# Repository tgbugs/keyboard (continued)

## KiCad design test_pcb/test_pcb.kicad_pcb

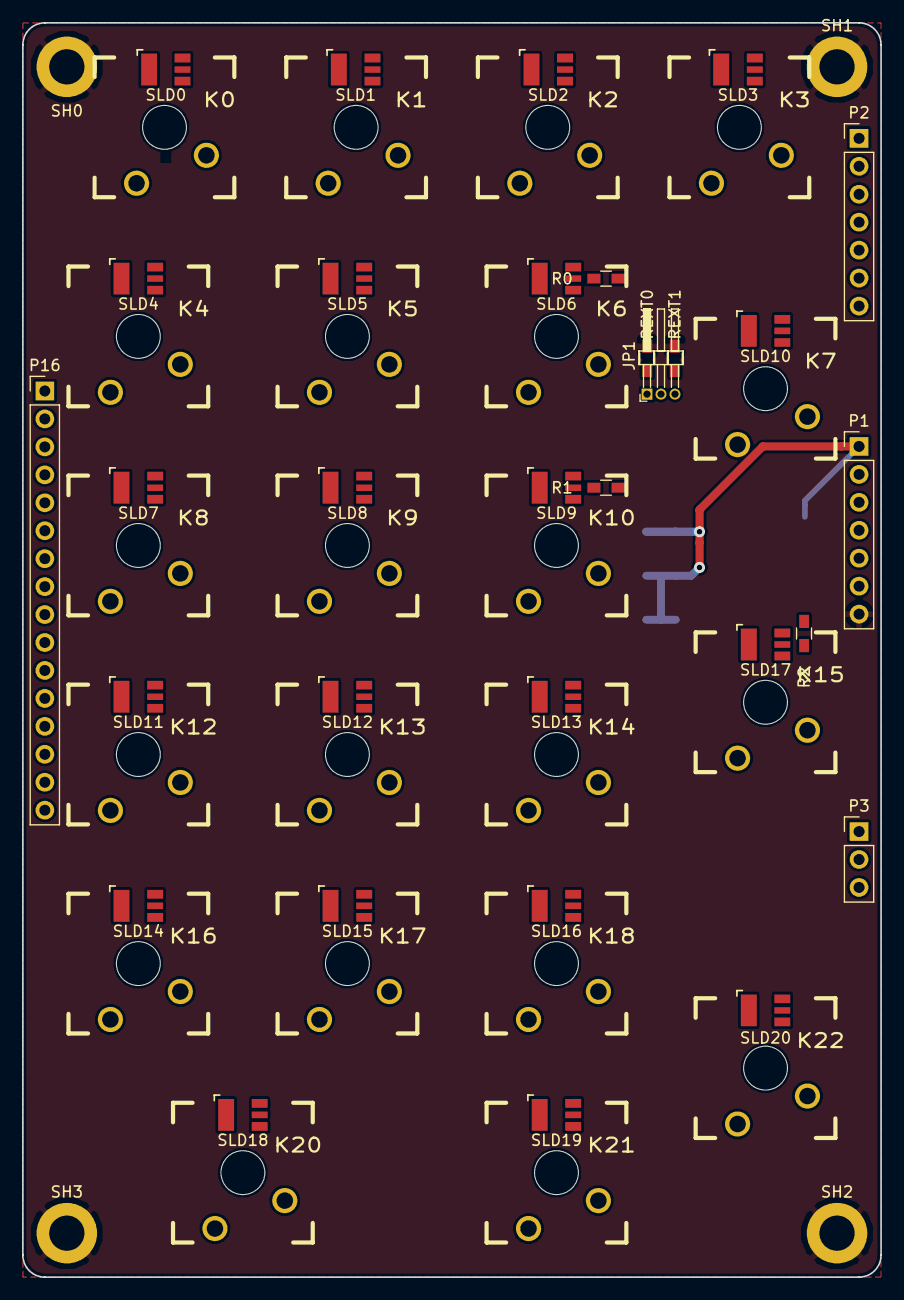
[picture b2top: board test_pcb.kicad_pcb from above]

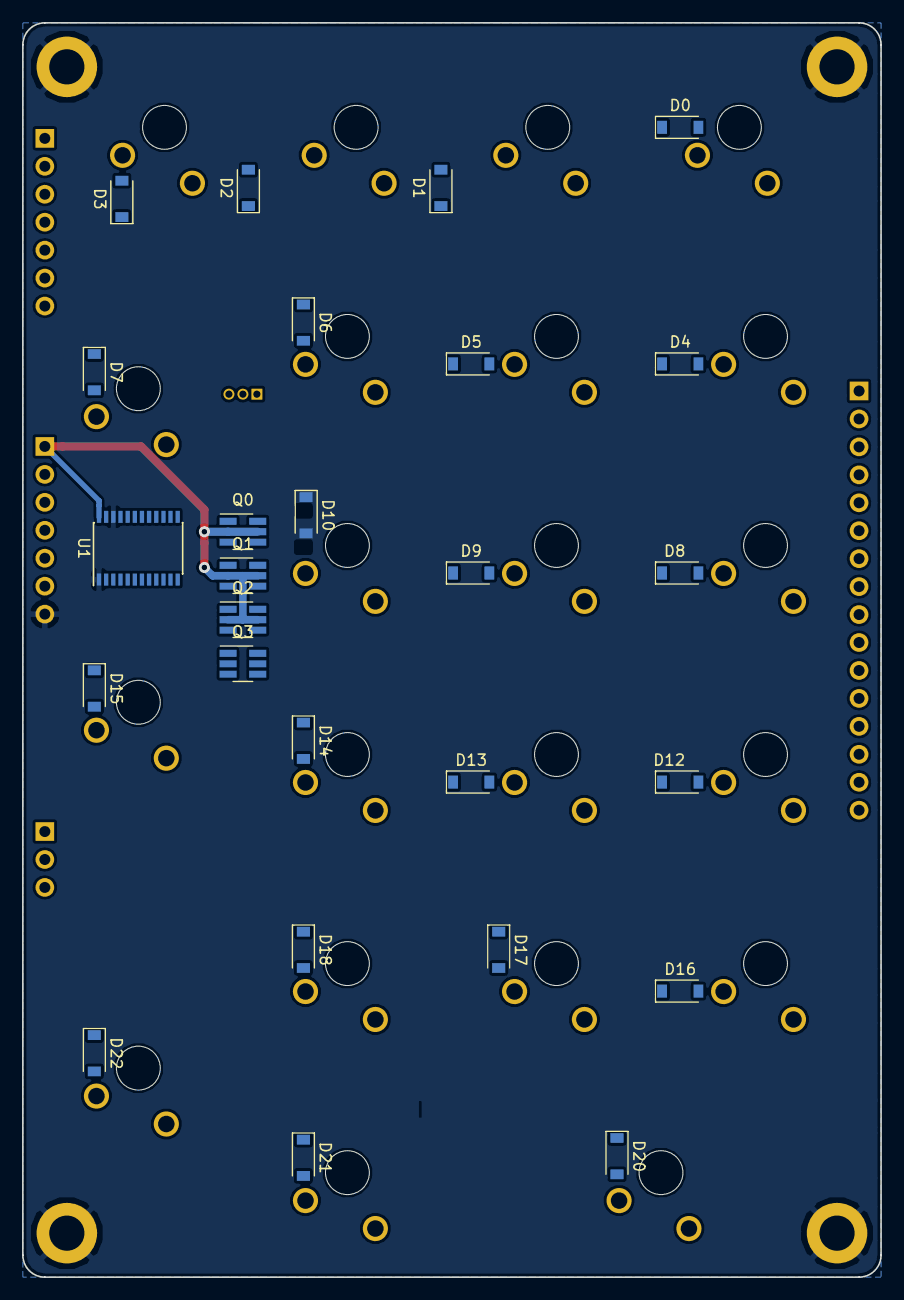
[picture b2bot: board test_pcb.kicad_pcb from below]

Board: 2 copper layers, 78.0 x 114.0 mm, 82 parts (26 on the bottom side), 66 nets.

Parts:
D0, D1, D2, D3, D4, D5, D6, D7, D8, D9, D10, D12, D13, D14, D15, D16, D17, D18, D20, D21, D22: D; D_SOD-123
JP1: Jumper_NC_Dual; Pin_Header_Angled_1x03_Pitch1.27mm
K0, K1, K2, K3: KEYSW; CHERRY_PLATE_91.6H
K4, K5, K6, K8, K9, K10, K12, K13, K14, K16, K17, K18, K21: KEYSW; CHERRY_PLATE_100H
K7, K15: KEYSW; CHERRY_PLATE_150V
K20: KEYSW; CHERRY_PLATE_200H
K22: KEYSW; CHERRY_PLATE_200V
P1, P2: CONN_01X07; Socket_Strip_Straight_1x07_Pitch2.54mm
P3: CONN_01X03; Socket_Strip_Straight_1x03_Pitch2.54mm
P16: CONN_01X16; Socket_Strip_Straight_1x16_Pitch2.54mm
Q0, Q1, Q2, Q3: Si3993CDV; SOT-23-6_Handsoldering
R0, R1, R2: R; R_0603_HandSoldering_label_right
REXT0, REXT1: R; R_0603_HandSoldering_label_right
SH0, SH1, SH2, SH3: CONN_01X01; MountingHole_3.2mm_M3_ISO14580_Pad
SLD0, SLD1, SLD2, SLD3, SLD4, SLD5, SLD6, SLD7, SLD8, SLD9, SLD11, SLD12, SLD13, SLD14, SLD15, SLD16, SLD18, SLD19, SLD20: SMLVN6RGB_CA
SLD10, SLD17: SMLVN6RGB; SMLVN6RGB_CA
U1: STP16CP05; TSSOP-24_4.4x7.8mm_Pitch0.65mm

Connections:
+3V3: P1.1, Q0.2, Q0.5, Q1.2, Q1.5, Q2.2, Q2.5, Q3.5, U1.24
CLK: P1.5, U1.3
GND: P1.7, REXT0.1, REXT1.1, SH0.1, SH1.1, SH2.1, SH3.1, U1.1, U1.22
LE: P1.4, U1.4
unnamed: D0.2, K0.2
unnamed: D1.2, K1.2
unnamed: D2.2, K2.2
unnamed: D3.2, K3.2
unnamed: D4.2, K4.2
unnamed: D5.2, K5.2
unnamed: D6.2, K6.2
unnamed: D7.2, K7.2
unnamed: D8.2, K8.2
unnamed: D9.2, K9.2
unnamed: D10.2, K10.2
unnamed: D12.2, K12.2
unnamed: D13.2, K13.2
unnamed: D14.2, K14.2
unnamed: D15.2, K15.2
unnamed: D16.2, K16.2
unnamed: D17.2, K17.2
unnamed: D18.2, K18.2
unnamed: D20.2, K20.2
unnamed: D21.2, K21.2
unnamed: D22.2, K22.2
unnamed: JP1.1, REXT0.2
unnamed: JP1.3, REXT1.2
unnamed: R0.2, U1.15
unnamed: R1.2, U1.16
unnamed: R2.2, U1.17
OE: P1.3, U1.21
SDI: P1.6, U1.2
a0: Q0.6, SLD0.1, SLD7.1, SLD14.1
a1: Q0.4, SLD1.1, SLD8.1, SLD15.1
a2: Q1.6, SLD2.1, SLD9.1, SLD16.1
a3: Q1.4, SLD3.1, SLD10.1, SLD17.1
a4: Q2.6, SLD4.1, SLD11.1, SLD18.1
a5: Q2.4, SLD5.1, SLD12.1, SLD19.1
a6: Q3.6, SLD6.1, SLD13.1, SLD20.1
as0: P16.7, Q0.1, U1.6
as1: P16.8, Q0.3, U1.7
as2: P16.9, Q1.1, U1.8
as3: P16.10, Q1.3, U1.9
as4: P16.11, Q2.1, U1.10
as5: P16.12, Q2.3, U1.11
as6: P16.13, Q3.1, U1.12
blue0: P16.1, SLD0.6, SLD1.6, SLD2.6, SLD3.6, SLD4.6, SLD5.6, SLD6.6, U1.20
blue1: P16.4, SLD7.6, SLD8.6, SLD9.6, SLD10.6, SLD11.6, SLD12.6, SLD13.6, U1.19
blue2: P16.14, SLD14.6, SLD15.6, SLD16.6, SLD17.6, SLD18.6, SLD19.6, SLD20.6, U1.18
c0: D0.1, D4.1, D8.1, D12.1, D16.1, D20.1, P2.1
c1: D1.1, D5.1, D9.1, D13.1, D17.1, P2.3
c2: D2.1, D6.1, D10.1, D14.1, D18.1, D21.1, P2.4
c3: D3.1, D7.1, D15.1, D22.1, P2.5
green0: P16.3, SLD0.4, SLD1.4, SLD2.4, SLD3.4, SLD4.4, SLD5.4, SLD6.4, U1.14
green1: P16.6, SLD7.4, SLD8.4, SLD9.4, SLD10.4, SLD11.4, SLD12.4, SLD13.4, U1.13
green2: P16.16, SLD14.4, SLD15.4, SLD16.4, SLD17.4, SLD18.4, SLD19.4, SLD20.4, U1.5
r0: K0.1, K1.1, K2.1, K3.1, P2.2
r1: K4.1, K5.1, K6.1, K7.1, P2.6
r2: K8.1, K9.1, K10.1, P2.7
r3: K12.1, K13.1, K14.1, K15.1, P3.1
r4: K16.1, K17.1, K18.1, P3.2
r5: K20.1, K21.1, K22.1, P3.3
red0: P16.2, R0.1, SLD0.5, SLD1.5, SLD2.5, SLD3.5, SLD4.5, SLD5.5, SLD6.5
red1: P16.5, R1.1, SLD7.5, SLD8.5, SLD9.5, SLD10.5, SLD11.5, SLD12.5, SLD13.5
red2: P16.15, R2.1, SLD14.5, SLD15.5, SLD16.5, SLD17.5, SLD18.5, SLD19.5, SLD20.5
rext: JP1.2, P1.2, U1.23

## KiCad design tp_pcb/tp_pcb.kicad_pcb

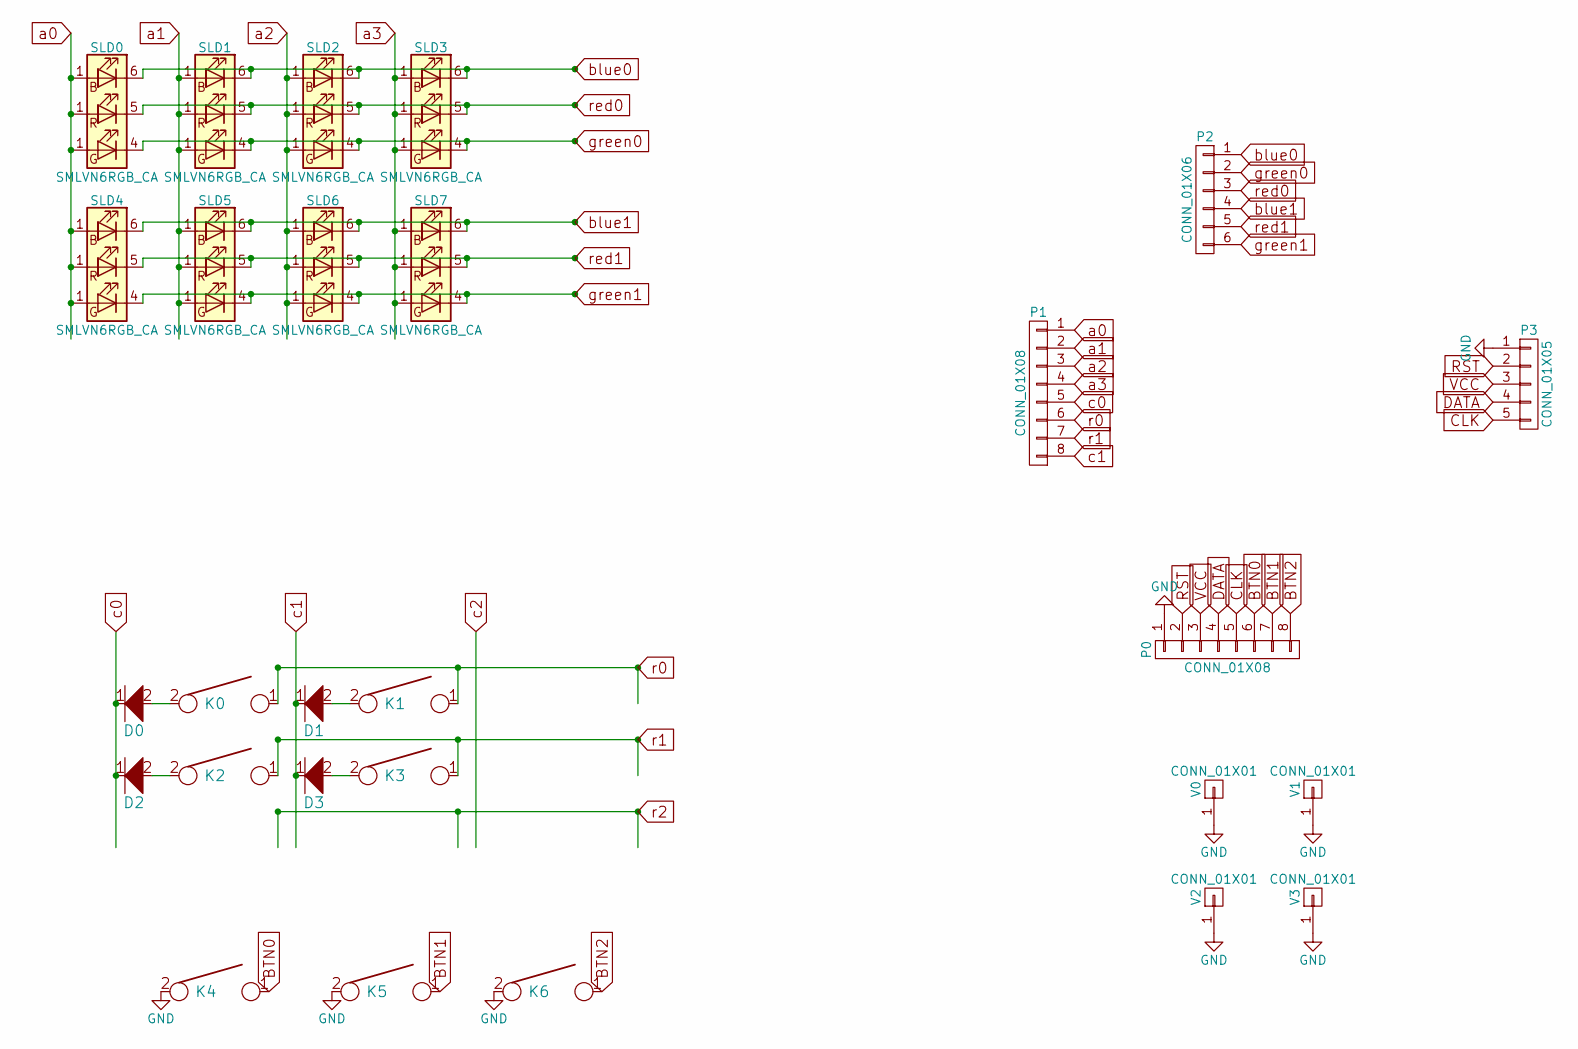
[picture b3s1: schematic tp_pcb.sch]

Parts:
D0, D1, D2, D3: D; D_SOD-123
K0, K1, K2, K5: KEYSW; CHERRY_PLATE_NH_100H
K3: KEYSW; CHERRY_PLATE_NH_5000H
K4, K6: KEYSW; CHERRY_PLATE_175H
P0: CONN_01X08; Molex_PicoBlade_53261-0871_08x1.25mm_Angled
P1: CONN_01X08; Socket_Strip_Straight_1x08_Pitch2.54mm
P2: CONN_01X06; Socket_Strip_Straight_1x06_Pitch2.54mm
P3: CONN_01X05; Socket_Strip_Straight_1x05_Pitch2.54mm
SLD0, SLD1, SLD2, SLD3, SLD4, SLD5, SLD6, SLD7: SMLVN6RGB_CA
V0, V1, V2, V3: CONN_01X01; VIA127

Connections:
BTN0: K4.1, P0.6
BTN1: K5.1, P0.7
BTN2: K6.1, P0.8
CLK: P0.5, P3.5
DATA: P0.4, P3.4
GND: K4.2, K5.2, K6.2, P0.1, P3.1, V0.1, V1.1, V2.1, V3.1
unnamed: D0.2, K0.2
unnamed: D1.2, K1.2
unnamed: D2.2, K2.2
unnamed: D3.2, K3.2
RST: P0.2, P3.2
VCC: P0.3, P3.3
a0: P1.1, SLD0.1 (BK), SLD4.1 (BK)
a1: P1.2, SLD1.1 (BK), SLD5.1 (BK)
a2: P1.3, SLD2.1 (BK), SLD6.1 (BK)
a3: P1.4, SLD3.1 (BK), SLD7.1 (BK)
blue0: P2.1, SLD0.6 (RA), SLD1.6 (RA), SLD2.6 (RA), SLD3.6 (RA)
blue1: P2.4, SLD4.6 (RA), SLD5.6 (RA), SLD6.6 (RA), SLD7.6 (RA)
c0: D0.1, D2.1, P1.5
c1: D1.1, D3.1, P1.8
green0: P2.2, SLD0.4 (BA), SLD1.4 (BA), SLD2.4 (BA), SLD3.4 (BA)
green1: P2.6, SLD4.4 (BA), SLD5.4 (BA), SLD6.4 (BA), SLD7.4 (BA)
r0: K0.1, K1.1, P1.6
r1: K2.1, K3.1, P1.7
red0: P2.3, SLD0.5 (GA), SLD1.5 (GA), SLD2.5 (GA), SLD3.5 (GA)
red1: P2.5, SLD4.5 (GA), SLD5.5 (GA), SLD6.5 (GA), SLD7.5 (GA)

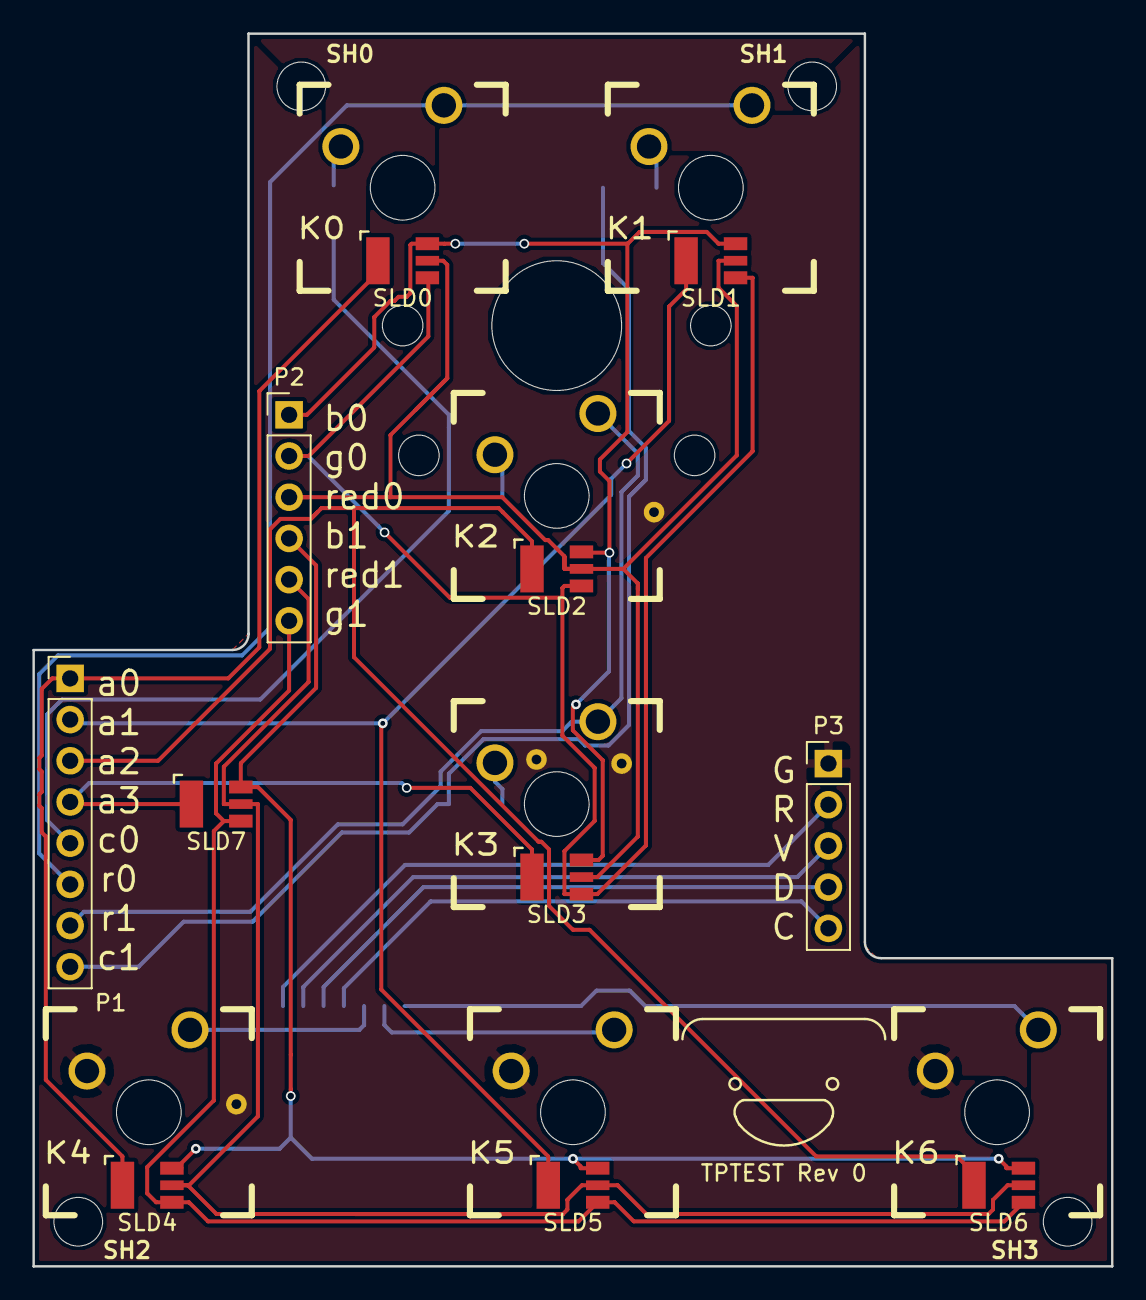
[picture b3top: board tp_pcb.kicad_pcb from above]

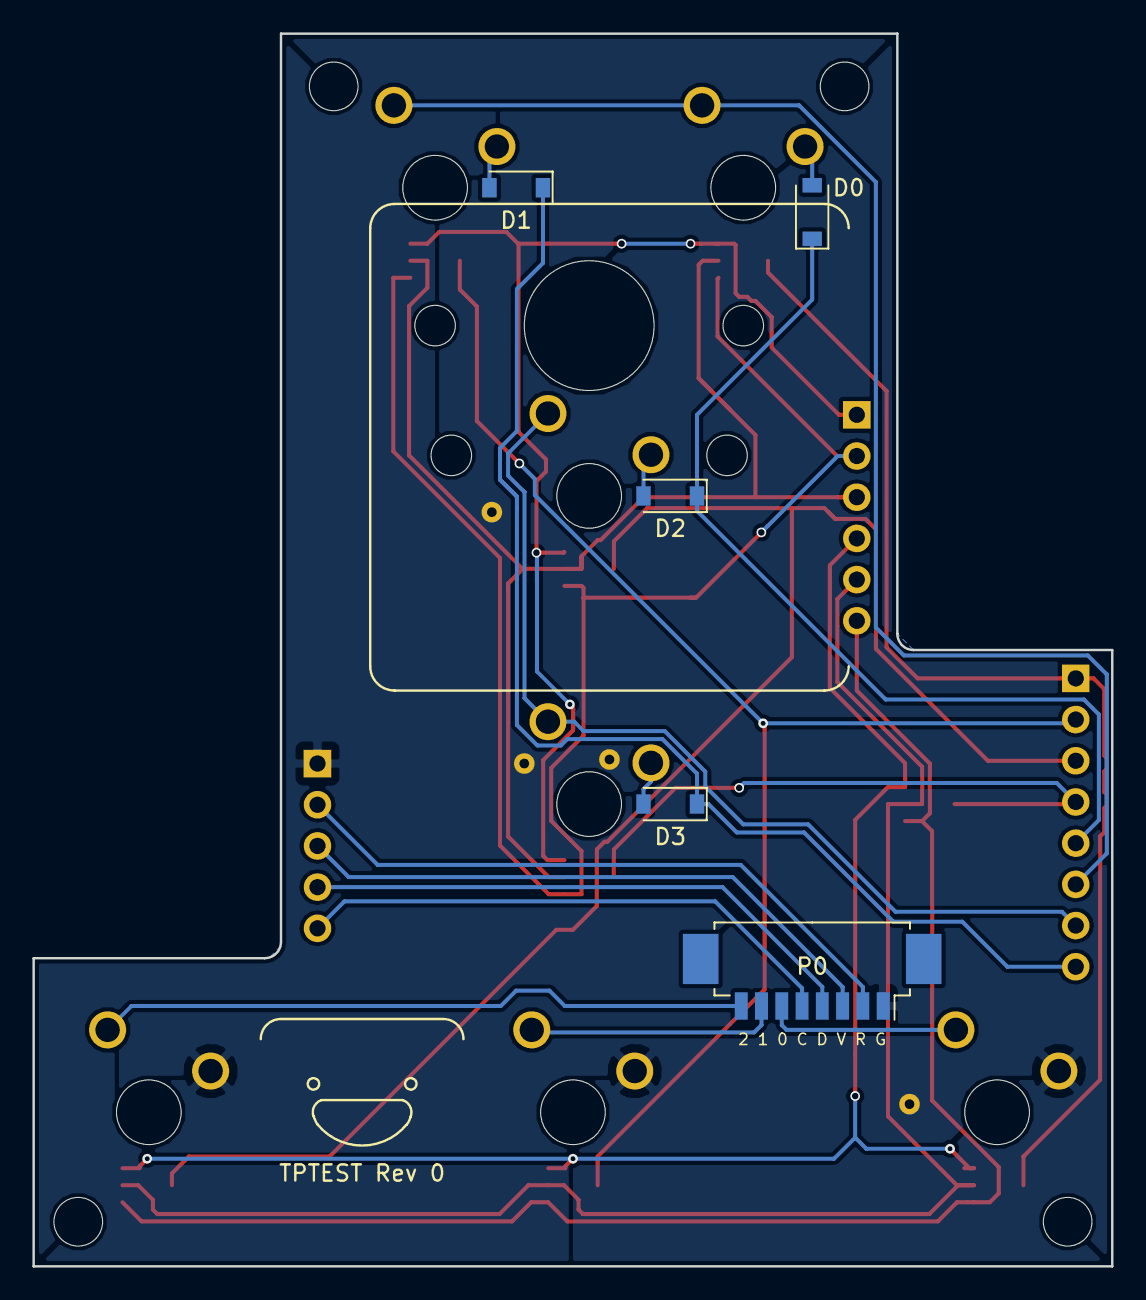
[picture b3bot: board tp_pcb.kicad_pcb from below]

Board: 2 copper layers, 66.5 x 76.0 mm, 34 parts (6 on the bottom side), 26 nets.

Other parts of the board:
LVC9_HOLES: LVC9 Attach; LVC9_HOLES_for_tptest
SH0, SH1, SH2, SH3: CONN_01X01; MOUNTING_HOLE
TPTEST Rev 0, TPTEST Rev 0#2: tgbugs_sig

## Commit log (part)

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2017-01-30 added additional keys
2017-01-31 parts provide
2017-01-31 some math on pin counts, assuming SMD is viable
2017-02-01 layout macro key and vim annotations
2017-02-03 LVC9 measured params
2017-02-03 leds and driver
2017-02-03 logic typo
2017-02-03 added custom_pcb kicad project
2017-02-03 added test_pcb kicad project
2017-02-03 added libs for individual parts for kicad
2017-02-03 added schematics (datasheets also go there)
2017-02-03 added .gitignore
2017-02-03 added README.md
2017-02-03 readme added link to guide
2017-02-04 updated test_pcb
2017-02-04 added LVC9_HOLES footprint for trackpoint placement
2017-02-06 test_pcb first pass complete
2017-02-06 custom_pcb first pass layout
2017-02-06 custom_pcb wiring and diode placement
2017-02-06 test_pcb small stuff
2017-02-06 LVC9 adjusted picture annotation to better fit the reality of working with the board
2017-02-06 updated counts to reflect changes in number of keys
2017-02-06 parts updated with additional considerations
2017-02-06 cpcb shifted diodes down 1mm to make routing rows easier
2017-02-06 cpcb wiring
2017-02-06 cpcb more routing
2017-02-07 improved and simplified layout
2017-02-07 cpcb switched to 7x14 matrix finished first pass routing
2017-02-07 cpcb routing of rows and columns complete
2017-02-07 added switch footprints with no holes, the buffer for makeing new length keys is .204 mm of padding
2017-02-07 added tgbugs_custom lib for chips I cant find online
2017-02-07 gitignore vim stuff
2017-02-07 wiring cleanup
2017-02-07 parts note
2017-02-07 libs added leds
2017-02-07 cpcb started led work
2017-02-07 cpcb led layout
2017-02-07 cpcb major improvements to trackpoint routing
2017-02-07 finished 2nd draft led wiring
2017-02-08 cpcb some cleanup of keys, offset by top routing getting messed up (needs to be reworked anyway), plus experiments on how to route individual BRG rows, need to experiment with all of a single color r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
2017-02-08 cpcb routing all same color turns out to be a much better idea, plus sync errors will appear to be shifts in hue rather than shifts in timing
2017-02-08 cpcb we dont need the diodes all the way up, much more room if hidden near the hole, only works at the margins
2017-02-08 simplified tp routing
2017-02-08 cpcb routing of blue traces and reworing of upper anodes
2017-02-09 cpcb improved routing of annodes and columns on the right side of the board
2017-02-09 notes on dev env
2017-02-09 LED_CLK routing and placement of the LED drivers so that they are all at the end of a 37mm track
2017-02-09 more routing
2017-02-10 blue tracks routed
2017-02-10 green routing
2017-02-10 red routed
2017-02-10 layout v4, not switching to this yet, merely here for further consideration
2017-02-10 routing tweaks to free up more space for reimplementing the teensy
2017-02-10 experiment with 11/12 width f keys, mich might just barely fit floating keycaps
2017-02-10 converted to an equivalent representation that has one fewer rows in hope of not confusing everything
2017-02-10 lv5 switched to using offsets instead of widths since the keys are technically still 1 unit, I'm just cheating at the level of the caps
2017-02-10 test experiment with 11/12ths keys
2017-02-10 11/12ths size key as an experiment
2017-02-10 all traces for the matrix are done
2017-02-10 equalized led clk distances
2017-02-10 started work on ground planes and rerouting the led tracks so that the via is on the anode saving 4 vias per led
2017-02-11 routing optimization
2017-02-11 notes about how ibm dealt with the trackpoint hole
2017-02-12 small updates
2017-02-12 numpad layout, will be used to test all components and strange key configurations needed for the full scale
2017-02-13 test is now a numpad for led testing + a 6 key test for the trackpoint
2017-02-13 lots of progress on numpad
2017-02-13 ground planes added
2017-02-14 when you use a contant current LED driver you don't actually need resistors!
2017-02-17 updates?
2017-02-17 200V footprint
2017-02-17 a svg for the numpad plate and some additional schematics
2017-02-17 test output holes
2017-02-21 matrix_control added for doing the math for controlling the led matrix
2017-02-21 added the teensy mcu datasheets for convenience
2017-02-21 added tp_pcb for prototyping the trackpoint part of the board
2017-02-24 tp_pcb routing, woo interactive
2017-02-24 cpcb tweaked
2017-02-24 cpcb freerouting files prior to completely reworking the circuitry
2017-02-24 cpcb wrote the output of freerouting for the record
2017-02-24 added common anode configuration for the led
2017-02-24 sch rewiring for leds
2017-02-24 cpcb good timepoint
2017-02-24 cpcb actually good timepoint
2017-02-25 test pcb freerouting is bugged on this right now
2017-02-25 test pcb some improvement, but still getting the infinite fails
2017-02-25 test pcb seem to have fixed the routing bug
2017-02-25 testp progress
2017-02-25 test a bit better
2017-02-25 test somehow improved routing adding 5 more and 1mm on the right side of the board
2017-02-25 test groud plane
2017-02-25 added flipped angled 01x02 header footprint
2017-02-25 test groundplanes
2017-02-26 test more gp
2017-02-26 test groundplane loop eliminiation
2017-02-26 test groundplane loop eliminiation, they are sneeky
2017-02-26 test ground planes nearing completion
2017-02-26 test gp tweaks
2017-02-26 test added 1mm to left to match that on right
2017-02-26 added 1.27mm vias and move the letters on some of the key footprints
2017-02-26 test updated key footprints
2017-02-26 libs updated to shorten led name
2017-02-26 gitignore no zips in the lib folder
2017-02-26 removed old project and sch, saving sch before rename
2017-02-26 led footprints updated so that silkscreen doesn't hit the nogo zone
2017-02-26 renaming leds and swapping footprints
2017-02-26 footprints silkscreen mods
2017-02-26 test ready to gerber?
2017-02-26 readme freeroute
2017-02-26 test mouting holes and sch cleanup and notes
2017-02-26 readme gerbv note
2017-02-26 footprints, signature and led orientation marking, added to board
2017-02-26 test silkscreen tweaks
2017-02-26 test NUMPAD rev 0 files which are to be submitted for fabrication
2017-02-26 tp major improvements + routing, tp holes improved and modified
2017-02-26 tp fixed naming issues
2017-02-26 tp outline moved to bsilk
2017-02-26 working on mounting holes
2017-02-26 tp adjusted mounting hole text
2017-02-26 tp groundplanes seem done
2017-02-26 spacebar silkscreen fix
2017-02-26 tp silkscreen touchup and a few final tweaks
2017-02-26 tp more tweaks
2017-02-26 tp rounded corners
2017-02-26 TPTEST Rev 0 gerbers
2017-02-26 tp some very minor change that was probably in rev0
2017-02-26 part note on led driver
2017-02-27 logic and gerber was missing drill files!
2017-02-27 layout to generate a plate for tptest
2017-02-27 parts note about plate for tptest
2017-02-27 tptest plate added
2017-02-27 cpcb lots more relestate down at the bottom for the control circuitry
2017-02-27 new layout considering a 2 vert for escape and delete since there is space and it will make them even easier to hit, also the 1.5 doesn't have stabilizers which could lead to problems
2017-02-27 this is going to be tricky until the matrix is rewired correctly to minimize distance, also if we cut out the lower part of the pcb we won't have all this space, so we may ultimately go back to the p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
2017-02-27 cpcb sch small changes?
2017-03-07 tgbugs_custom added transistor and added datasheets to existing entries
2017-03-07 libs added dual p channel
2017-03-07 test first pass manual routing of anodes for rev 1
2017-03-07 test routing complete, this is a pre application checkpoint
2017-03-07 test large loop check passed
2017-03-07 cpcb updated led positions
2017-03-07 cpcb starting to rework led positioning to minimize wiring
2017-03-07 cpcb transistors
2017-03-07 cpcb hints to improve autorouting
2017-03-08 cpcb sane pin orderings
2017-03-08 added other teensy 3.2 parts, left out a bunch of the analog stuff
2017-03-08 cpcb timepoint before major led routing rework
2017-03-08 removed old routed dsn file that is no longer part of the workflow
2017-03-08 routing of the tricky bits and discovered and added the MKL04Z32
2017-03-08 cpcb more sane pin ordering
2017-03-08 module for MKL04 and more routing
2017-03-08 cpcb routing completed, saving as a reference
2017-03-08 shifted controller circuitry down by 1.25mm
2017-03-08 cpcb and footprints updated for major reworking (all switches rotated 180, thanks ducky\!)
2017-03-08 small fixes and checkpoint for moving the leds
2017-03-08 missing backup
2017-03-08 moved all the leds woo regex
2017-03-09 placement and routing
2017-03-09 flipped keys that were previously missed
2017-03-09 led positions are now sane
2017-03-09 diode placement
2017-03-09 anode routing
2017-03-09 backup, checkpoint for optimizing key locations in the matrix
2017-03-09 keyboard matrix layout fixed
2017-03-09 work on rows
2017-03-09 manual routing of the tricky bits
2017-03-09 routing and pin ordering
2017-03-09 tricky routing
2017-03-09 rows
2017-03-09 start of row hookup
2017-03-09 lc1 pin ordering and routing
2017-03-09 power and ground
2017-03-09 more tricky routing
2017-03-09 more fanout routing
2017-03-09 more trickiy
2017-03-09 row routing, observe the dinosaur/cow
2017-03-09 was missing latch
2017-03-09 accidentally mirrored the power supply
2017-03-09 more tricky
2017-03-09 completed routing on lc2 and lc0, madness
2017-03-09 ALL THE GROUNDS
2017-03-09 issue was inaccessible track on sld79
2017-03-09 r1 was not sitting on its pin
2017-03-09 columns
2017-03-10 routing complete, load for debug
2017-03-10 more optimization passes
2017-03-10 first pass at fixing lc0 pinout ordering
2017-03-10 gp and row ordering bug
2017-03-10 routing tweaks for gp etc
2017-03-10 push routing mode is dangerous, it can move tracks into positions that cause infinite looping in freerouter because they block all ways to access a pad
2017-03-10 seems that there was a connected/disconnected track that was causing bugs
2017-03-10 moved schematics to the doc folder
2017-03-10 fixed crystal ground plane to match https://www.pjrc.com/store/ic_mkl02.html and https://forum.pjrc.com/threads/27397-Teensy-gt-Production?p=60903&viewfull=1#post60903
2017-03-10 clock signal traces to same length
2017-03-11 major rerouting to avoid any signals near the crystal and to get the rext resistors away from the led drivers
2017-03-11 optimization around led drivers
2017-03-11 more close in optimization
2017-03-11 about the move the mcu a few units to the left to free up some space
2017-03-11 progress!
2017-03-11 lots of fine routing work
2017-03-11 routing
2017-03-11 column routing
2017-03-11 found a better way to get power and anodes around
2017-03-11 compacted routing
2017-03-12 about to try an alternate rout
2017-03-15 bak file
2017-03-15 test new footprints (the 180 variety) and new design rules
2017-03-15 logic for rest in parallel, but ultimately go with series since the setup is safer if the attempt fails, also consdering trying to put everything on the front for real smd
2017-03-17 cpcb footprint for the 2 DIP switch
2017-03-17 routing tweaks for gnd plane
2017-03-17 tweaks
2017-03-17 more tweaks
2017-03-17 tweak was correct this time >_<
2017-03-17 columns wired
2017-03-17 tweaks to preserve gp
2017-03-17 more gp
2017-03-17 dsn file
2017-03-17 determining power and figured out that for usb c we need a thing called a configuration channel (cc) control logic
2017-03-17 reworked power and did some routing that could make it possible to control the led output levels using transistors as switches instead of the dip switch, dependent on getting the usb c cc working
2017-03-30 ah gate resistors, why did no one tell me about you, solution is 402
2017-10-10 added vis of current layout
2018-08-01 v7 layout
2018-08-01 the answer to 'do you ever use right shift?'
2018-08-01 readme added kle as a reminder to self
2018-08-03 v9 layout
    90 switches
    media keys, normal width fkeys, swapable f12/delete, tiny right shift
2018-08-03 v10 wide version
    2 keys to spare
